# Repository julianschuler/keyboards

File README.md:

# Keyboards

This repository contains the code, cases and co. of the keyboards I have built.

All keyboards in chronological order:

| Name                        | Image                                                 | Description                                                                        |
| --------------------------- | ----------------------------------------------------- | ---------------------------------------------------------------------------------- |
| [Manuform](manuform/)       |           | 50% hand-wired keyboard focussed on ergonomic typing with ortholinear columns      |
| [Ergomin](ergomin/)         |              | 40% PCB based split keyboard focussed on ergonomic typing with ortholinear columns |
| [Concavum](concavum/)       |           | Fully parametric ergonomic split keyboard with automatically generated matrix PCB  |
| [Concavum v2](concavum-v2/) |  | Second revision of the Concavum keyboard with an easy to use customizer            |

## License

This project is licensed under the MIT license, see [`LICENSE.txt`](LICENSE.txt) for further information.

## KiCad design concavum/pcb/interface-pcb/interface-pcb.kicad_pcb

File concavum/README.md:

# Concavum

## Overview
The Concavum is a fully parametric split keyboard featuring an ergonomic layout with ortholinear (non-staggered) columns and concave key wells.

It can be adjusted to have 1-5 rows, 2-6 columns and 1-6 thumb keys per half and provides a script to automatically generate a PCB for the key matrix, so no hand-wiring is required.

Each half has thus 2 PCBs: The automatically generated matrix PCB, which is dependent on key count, offsets, etc., and a generic interface PCB which can be used for all sizes. Both PCBs are connected internally using a FPC cable, the halves are connected externally through a TRRS cable.

## Building the keyboard
### Parts list (excluding the PCBs and complementary components)
The amount of switches and keycaps depends on the number of rows, columns and thumb keys.
* 6-72x keyboard switches (Cherry MX, Gateron, etc.)
* 2-60x DSA keycaps 1U
* 2-12x DSA keycaps 1.5U
* 8x countersunk screws M3x8
* 8x nuts M3
* 8x rubber feet
* 1x TRRS to TRRS cable 30cm (make sure it is the 4-pole variant)
* ~150-350g of PETG filament for the 3D printed case (heavily dependent on the size)

### Adjusting the keyboard
The first step in building a Concavum is to adjust the keyboard to your hand.
Start by installing [OpenSCAD](https://openscad.org/downloads.html) if not already done.
Open the file `case/concavum-case.scad` in OpenSCAD and switch to the Customizer (`Window > Customizer`). Select the preset with the name `keyboard-paramters` in the first drop down menu (the preview should now show a cluster with 6 columns and 3 rows).

Now you can start adjusting the keyboard to your needs, the default values adjusted to my hands should provide a good starting point. Always save your changes to the preset `keyboard-parameters` as the values of this preset will be used for the automatic matrix PCB generation later.

### Printing and testing the case
When you are done with your modifications, render the Case using `F6` and export it as STL or AMF.
Support material is required for printing. However, use support blockers for the nut holders as it is nearly impossible to remove support material from their inside. You can find example print files under [`case/example-print-files`](case/example-print-files) which should give an idea on how to adjust the support material and print settings.

It is highly recommended to print only one half for now, adding the switches and keycaps and testing the feel first. It may take a few iterations, really take your time to find a configuration that fits your hands!

If you are happy with your configuration, you can now print the second half and add the remaining switches and keycaps.

The bottom plate of the keyboard can either be 3D printed as well or e.g. cut out of aluminum. It can thus be either exported as a 3D object or outline using
```
python3 case/export-bottom-plate.py [output file name]
```
where the file extension determines its type (e.g. `bottom-plate.amf` or `bottom-plate.dxf`). In case of cutting, chamfer the holes afterwards using a countersink drill bit to allow the screw heads to sit flush later.

### Generating the PCB
To generate the matrix PCB, install [KiCad 7.0](https://www.kicad.org/download/) and [Python 3](https://www.python.org/downloads/). Afterwards, switch to the `pcb` subfolder and install the Python dependencies by executing
```
python3 -m pip3 install -r requirements.txt
```
You can now generate the matrix PCB using
```
python3 generate-matrix-pcb.py
```
and afterwards export the gerber files for both the matrix and interface PCBs using

```
python3 export-compressed-gerber.py
```

When exporting the gerber files, a DRC is performed. If there is no output, everything worked as expected. If you still would like to inspect the generated matrix PCB, you can open the PCB file using PcbNew (the PCB editor of KiCad):
```
pcbnew matrix-pcb/matrix-pcb-panel.kicad_pcb
```

#### Ordering the PCBs and complementary components
After exporting, you will find two zip files in the `gerber` subfolder: One for the interface PCB and one for the generated matrix PCB.

The two PCB types require different thicknesses: 0.6mm for the matrix PCB and 1.6mm for the interface PCB.
You need at least 2 boards of each type (one type of board for each half).

> **Note:** For the matrix PCB, your PCB manufacturer has to support track widths and minimum clearances of 0.15mm each. In the special case of keyboards with the maximum number of rows, tracks and minimum clearances of 0.13mm each have to be supported.

### Assembly
First, insert the M3 nuts into their holders (you may need to remove a few keys if you have already assembled those during testing).
Afterwards, add the key switches while ensuring that the orientation of the pins is aligned with the holes of the matrix PCB.

To assemble the PCBs, take two interface and two matrix PCBs and lay them each down with different sides facing up. Now you can solder the complementary SMD components onto all four PCBs.
**Important: Only solder the SMD components to the top of each PCB! Otherwise the keyboard will not work!**

*Assembled PCBs and FPC connectors needed for the whole keyboard, with the rails and tabs still connected for the left matrix PCB. The interface PCBs shown are from the deprecated ATmega32u4 variant.*

Afterwards, you can carefully break off the rails and tabs of the matrix PCBs, ideally over an edge. You can now fit the matrix PCBs into the cases, the sides with the diodes and FPC connector facing outwards.
The matrix PCB has to be bend during this procedure. Therefore, start to solder the switches at the top row and work your way down to the bottom rows and the thumb cluster.

Finally, you can add the FPC cables to connect the interface and matrix PCBs of each half and slide the interface PCBs into their dedicated holders.

*Fully assembled keyboard without bottom plates, on the left a half with the (now deprecated) ATmega32u4 variant is shown, on the right the KB2040 variant can be seen.*

The keyboard can now be closed up by screwing on the bottom plate and attaching the rubber feet.

## Building the firmware
### Setting up QMK
The firmware is powered by QMK, [install QMK](https://docs.qmk.fm/#/newbs_getting_started) if not already done.
After the installation, it is necessary to add a symlink to the `qmk` subfolder of this repository to the QMK `keyboards` directory, for linux e.g by
```
ln -s /path/to/concavum/qmk /path/to/qmk/keyboards/concavum
```

Now you should be able to compile the keyboard firmware by executing
```
qmk compile -kb concavum -km default
```

Make sure to have a look at the excellent [QMK documentation](https://docs.qmk.fm/#/newbs_building_firmware) on how to create your own keymap.

### Adjusting the keymap
After creating your first keymap, you can start by setting `MATRIX_ROWS`, `MATRIX_COLS` and `THUMB_KEYS` in `qmk/keymaps/<github_username>/config.h` according to your keyboard matrix.

Next, head over to `qmk/keymaps/<github_username>/keymap.c` and adjust the keymap to your liking. Make sure the amount of keys is correct, especially when you modified the above values compared to the default.

When you are finished, you can connect the keyboard via USB.
Put the KB2040 into the bootloader mode by holding the boot button and tapping the reset button, the KB2040 should now show up as a flash drive. After mounting the drive you can flash the firmware using
```
qmk flash -kb concavum -km <github_username>
```

### Reflashing the firmware
When flashing e.g. a new keymap to the Concavum, it has to be put into the bootloader mode. This can be done by hitting a key with the `QK_BOOT` keycode or double tapping the reset button on the KB2040. By default, this `QK_BOOT` keycode can be activated by holding both outermost thumb keys and hitting the key in the lower left corner.

It is highly recommended to keep this `QK_BOOT` keycode in any keymap you create as the physical reset button can only be accessed with the bottom plate removed.

## License

This project is licensed under the MIT license, see [`LICENSE.txt`](../LICENSE.txt) for further information.

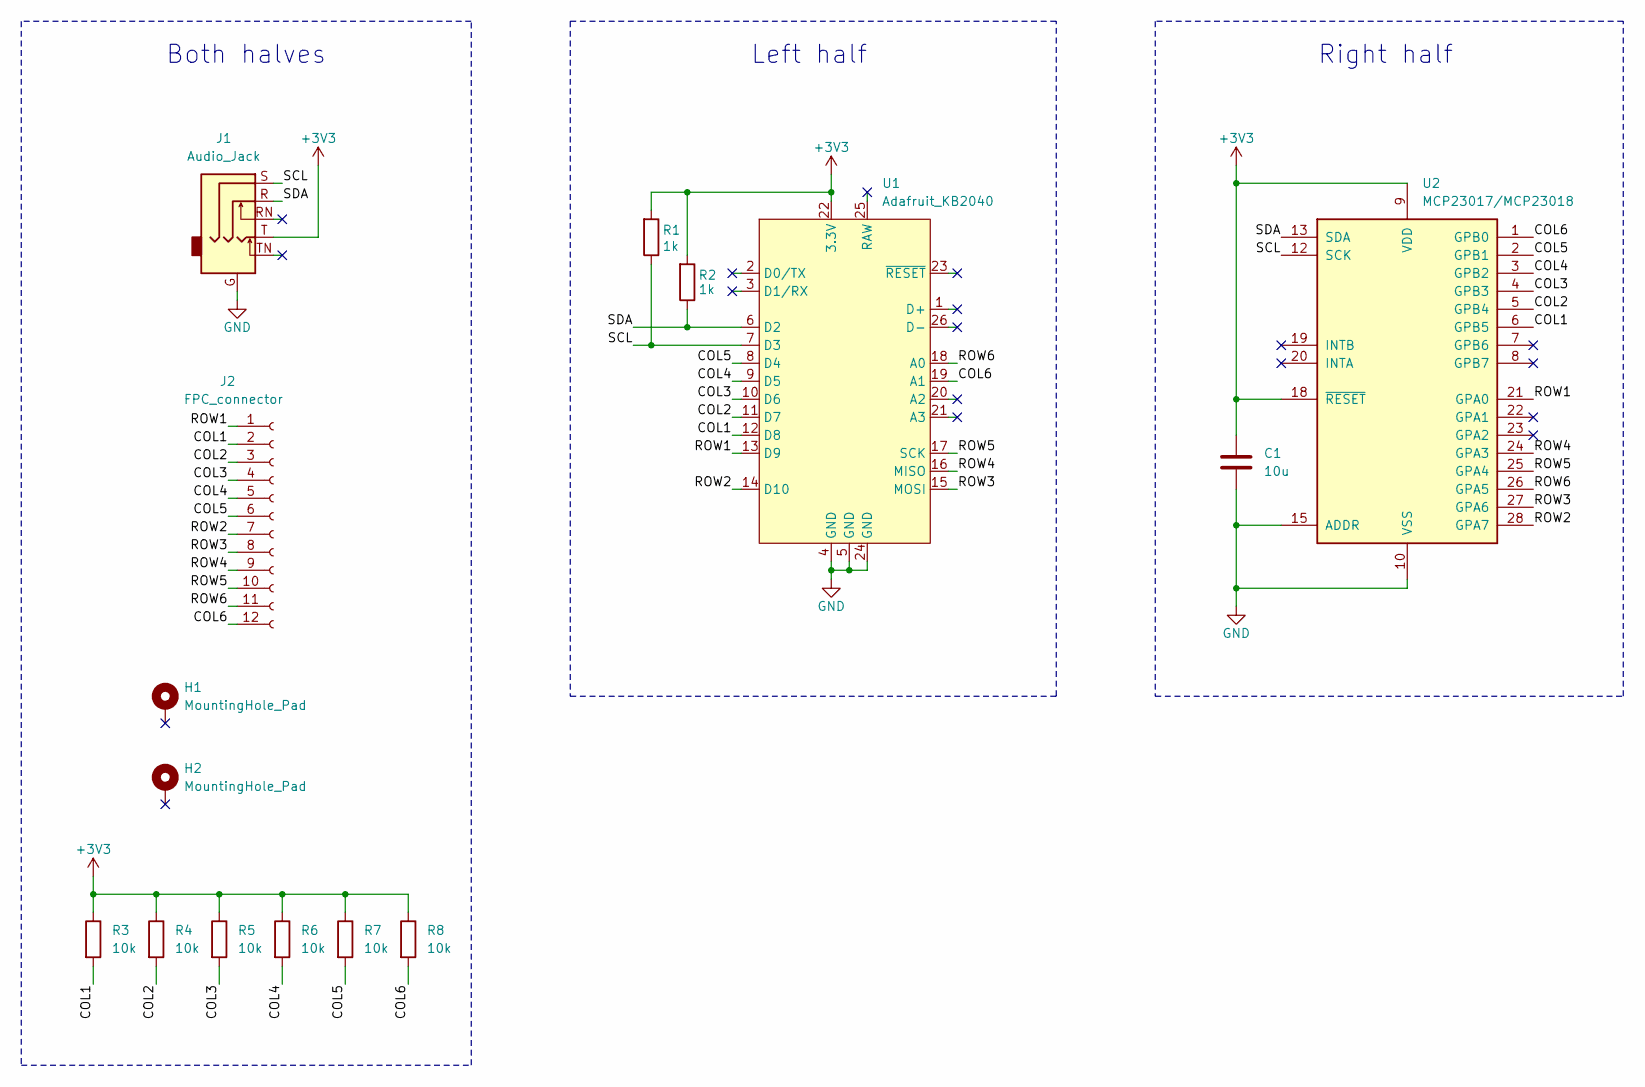
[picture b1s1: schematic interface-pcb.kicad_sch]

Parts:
C1: 10u; C_1206_3216Metric
H1, H2: MountingHole_Pad; MountingHole_2.2mm_M2_Pad_Via
J1: Audio_Jack; Audio_Jack_Dual_Side
J2: FPC_connector; FPC_Connector
R1, R2: 1k; R_1206_3216Metric
R3, R4, R5, R6, R7, R8: 10k; R_1206_3216Metric
U1: Adafruit_KB2040
U2: MCP23017/MCP23018; MCP23017_SO_MCP23018_SO

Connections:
+3V3: C1.1, J1.T, R1.2, R2.2, R3.1, R4.1, R5.1, R6.1, R7.1, R8.1, U1.22 (3.3V), U2.9 (VDD), U2.18 (~RESET)
/COL1: J2.2, R3.2, U1.12 (D8), U2.6 (GPB5)
/COL2: J2.3, R4.2, U1.11 (D7), U2.5 (GPB4)
/COL3: J2.4, R5.2, U1.10 (D6), U2.4 (GPB3)
/COL4: J2.5, R6.2, U1.9 (D5), U2.3 (GPB2)
/COL5: J2.6, R7.2, U1.8 (D4), U2.2 (GPB1)
/COL6: J2.12, R8.2, U1.19 (A1), U2.1 (GPB0)
/ROW1: J2.1, U1.13 (D9), U2.21 (GPA0)
/ROW2: J2.7, U1.14 (D10), U2.28 (GPA7)
/ROW3: J2.8, U1.15 (MOSI), U2.27 (GPA6)
/ROW4: J2.9, U1.16 (MISO), U2.24 (GPA3)
/ROW5: J2.10, U1.17 (SCK), U2.25 (GPA4)
/ROW6: J2.11, U1.18 (A0), U2.26 (GPA5)
/SCL: J1.S, R1.1, U1.7 (D3), U2.12 (SCK)
/SDA: J1.R, R2.1, U1.6 (D2), U2.13 (SDA)
GND: C1.2, J1.G, U1.4 (GND), U1.5 (GND), U1.24 (GND), U2.10 (VSS), U2.15 (ADDR)

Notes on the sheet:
Right half
Left half
Both halves

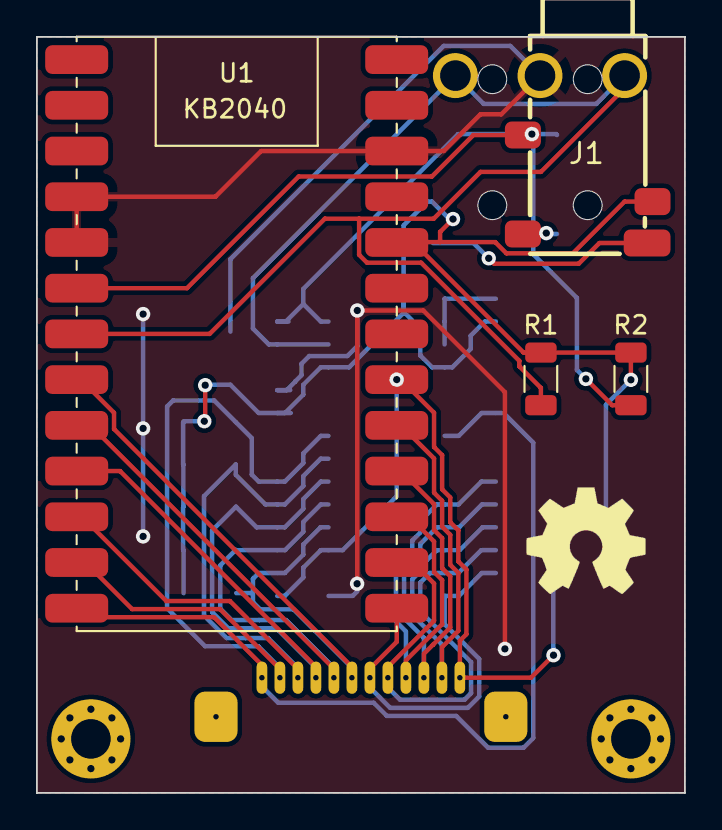
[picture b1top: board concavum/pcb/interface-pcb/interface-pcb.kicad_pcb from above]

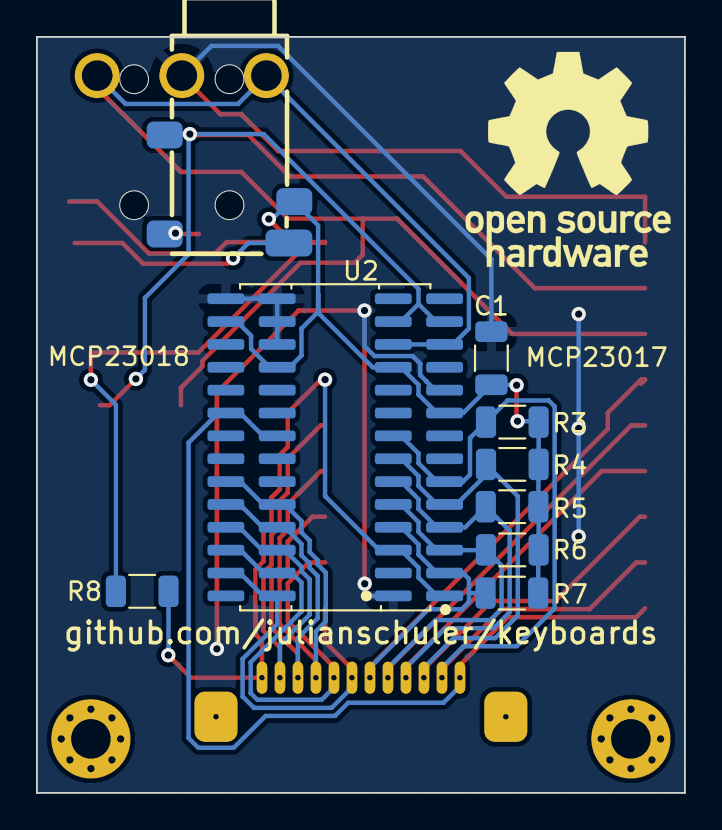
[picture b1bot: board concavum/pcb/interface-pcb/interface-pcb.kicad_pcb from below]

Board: 2 copper layers, 36.0 x 42.0 mm, 15 parts (8 on the bottom side), 16 nets.

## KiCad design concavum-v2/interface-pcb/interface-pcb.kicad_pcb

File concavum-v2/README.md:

# Concavum v2

## Overview

The Concavum v2 is a fully parametric split keyboard featuring an ergonomic layout with ortholinear (non-staggered) columns and concave key wells.

The centerpiece of the Concavum v2 is its customizer: It allows for changing all kinds of parameters like the number of columns, rows and thumb keys, the curvature, the distance between keys and many more.
It generates 3D printing files for the case, a PCB for connecting the key switches and configuration files for the keyboard firmware.

## Building your own

First, use the [Concavum customizer](https://github.com/julianschuler/concavum-customizer) to configure your Concavum to your liking.

When you are finished with configuring the keyboard, use the export button at the top right of the configuration panel to export all model files.
Extract the exported ZIP archive to a folder and switch to it.

### Parts list

You can find a detailed parts list in the file `bom.csv` in the export.

### Case

The case of the Concavum is 3D printed, you can find the corresponding files in the `case` subfolder of the export.
Since both halves are symmetric, only the 3D printing files for the right half are included in the export.
Mirror the files along the X axis in your slicer to print the left half.

The cases of both halves should be printed in the default orientation and using support material.
For my build, I used [Prusament PETG Galaxy Black](https://www.prusa3d.com/product/prusament-petg-prusa-galaxy-black-1kg/).

The bottom plates may either be 3D printed or laser cut.
Currently, the customizer only exports a 3D printing file for the bottom plate.
You can use [OpenSCAD](https://openscad.org/) with the provided `bottom_plate_to_dxf.scad` script to generate a DXF file for laser cutting:

```sh
openscad -o bottom_plate.dxf bottom_plate_to_dxf.scad
```

For my build, I ordered the bottom plates to be laser cut out of 3mm thick aluminum sheet.

### PCBs

The Concavum uses two types of PCBs in each half.
The interface PCB houses the keyboard controller, a TRRS and FFC connector and is the same for all Concavum keyboards.
You can find the KiCAD files of the interface PCB in the [`interface-pcb`](interface-pcb) subfolder of this repository.

The matrix PCB is generated by the customizer and specific to each keyboard.
It connects all keys in a matrix and connects to the interface PCB using an FFC cable.

For manufacturing, some break-away tabs should be added to the matrix PCB.
You can generate these tabs using [KiKit](https://yaqwsx.github.io/KiKit/latest/).
Start by [installing the KiKit backend](https://yaqwsx.github.io/KiKit/latest/installation/intro/) and execute the following command in the `pcb` folder of the exported files:

```sh
kikit panelize -p kikit_parameters.json matrix_pcb.kicad_pcb matrix_pcb_panelized.kicad_pcb
```

> [!TIP]
> You can also use KiKit to generate the gerber files from the KiCad files:
> ```sh
> kikit export gerber matrix_pcb_panelized.kicad_pcb matrix_pcb
> kikit export gerber interface_pcb.kicad_pcb interface_pcb
> ```

The two PCB types require different thicknesses.
When ordering, select 0.6mm for the matrix PCB and 1.6mm for the interface PCB.
You need at least 2 boards of each type, one of each type per half.

### Assembly

First, install the heat set inserts into the provided holes.
Add the key switches to the case, making sure that the orientation of the pins is aligned with the holes in the matrix PCB.

Next, assemble the interface and matrix PCBs.
All PCBs are designed to be assembled from only one side.
Lay down two pairs of interface and matrix PCBs with different sides facing up in each pair.
Solder all components on the top facing sides of each PCB, leaving the respective bottom sides unpopulated.
The assembled PCBs should be symmetric to each other.

Afterwords, carefully break off the tabs of the matrix PCBs.

*Picture of the assembled matrix and interface PCBs for both halves, with the tabs of the left matrix PCB still connected. The FFC cables connecting the matrix and interface PCBs within each half are shown below the right matrix PCB.*

Insert the matrix PCBs into the cases such that the sides with the diodes and FFC connector face outwards.
For each half, solder the matrix PCB to all keys, pushing it against each key while soldering.
Start with the home row and work your way up and down the columns and to the thumb cluster.

Finally, connect the interface and matrix PCBs of each half using the FFC cables and insert the interface PCBs into their dedicated holders.

*Picture of the fully assembled keyboard without bottom plates. Depending on the thumb cluster position, introducing a loop into the FFC cables as shown in the picture may be necessary to avoid kinks in the cables.*

Use a chamfer bit to create countersinks in the bottom plate holes to make the screws sit flush with them.
Screw on the bottom plate and attach the rubber feet to finish the build.

## Firmware

### Setting up QMK

The firmware is powered by QMK, [install QMK](https://docs.qmk.fm/#/newbs_getting_started) if not already done.

After the installation, rename the `qmk` folder of the export to `concavum` and move it to the `keyboards` folder in the QMK home.

You should now be able to compile the keyboard firmware using the following:

```sh
qmk compile -kb concavum -km default
```

Make sure to have a look at the excellent [QMK documentation](https://docs.qmk.fm/#/newbs_building_firmware) on how to create your own keymap.

### Flashing

To flash the firmware to the Concavum, connect the left half via USB and put the KB2040 into DFU mode by holding the boot button and tapping the reset button.
The KB2040 should now show up as a flash drive.

Mount the drive and flash the default firmware using the following:

```sh
qmk flash -kb concavum
```

Repeat the same process for the right half.

### Reflashing

To for example update the keymap, the firmware has to be reflashed.
When QMK is running on the Concavum, there are multiple ways to put the keyboard into DFU mode for reflashing:

- Press a key with the `QK_BOOT` keycode (not present in the default keymap)
- For the left half: Hold down the top left key when plugging the left half in
- For the right half: Hold down the top right key when plugging the right half in
- Double tap the reset button on the KB2040 (requires removing the bottom plate)

## License

This project is licensed under the MIT license, see [`LICENSE.txt`](../LICENSE.txt) for further information.

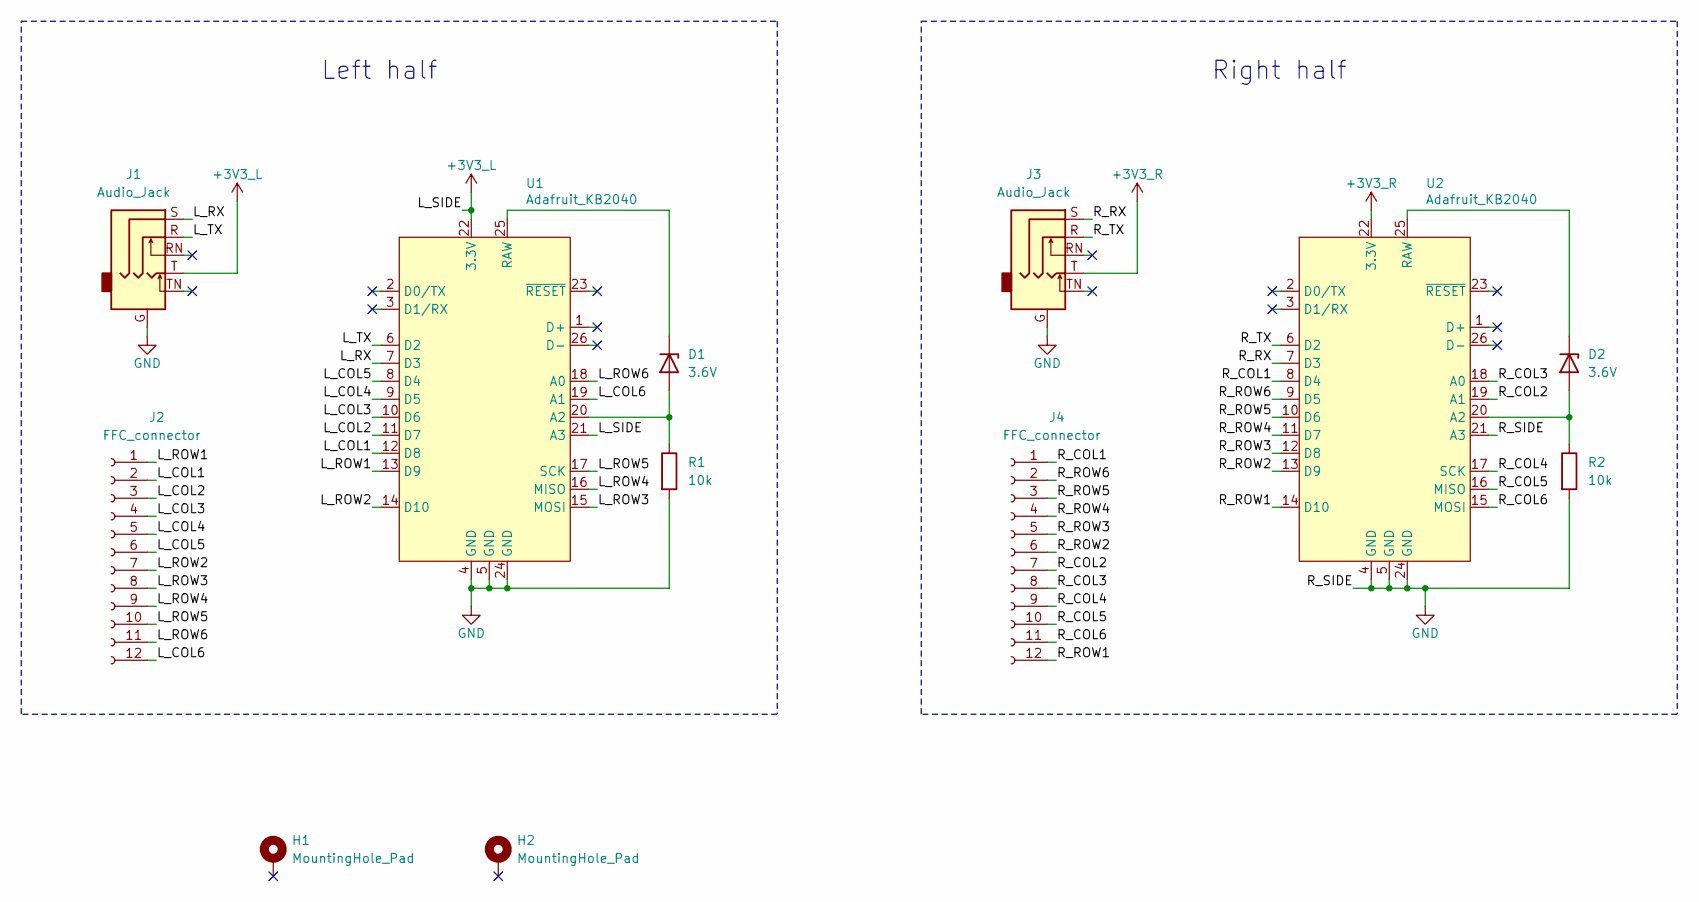
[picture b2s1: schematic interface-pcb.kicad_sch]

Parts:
D1, D2: 3.6V; D_MiniMELF
H1, H2: MountingHole_Pad; MountingHole_2.2mm_M2_Pad_Via
J1, J3: Audio_Jack
J2, J4: FFC_connector; FPC_Connector
R1, R2: 10k; R_1206_3216Metric
U1, U2: Adafruit_KB2040

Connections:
+3V3_L: J1.T, U1.21 (A3), U1.22 (3.3V)
+3V3_R: J3.T, U2.22 (3.3V)
/L_COL1: J2.2, U1.12 (D8)
/L_COL2: J2.3, U1.11 (D7)
/L_COL3: J2.4, U1.10 (D6)
/L_COL4: J2.5, U1.9 (D5)
/L_COL5: J2.6, U1.8 (D4)
/L_COL6: J2.12, U1.19 (A1)
/L_ROW1: J2.1, U1.13 (D9)
/L_ROW2: J2.7, U1.14 (D10)
/L_ROW3: J2.8, U1.15 (MOSI)
/L_ROW4: J2.9, U1.16 (MISO)
/L_ROW5: J2.10, U1.17 (SCK)
/L_ROW6: J2.11, U1.18 (A0)
/L_RX: J1.S, U1.7 (D3)
/L_TX: J1.R, U1.6 (D2)
/R_COL1: J4.1, U2.8 (D4)
/R_COL2: J4.7, U2.19 (A1)
/R_COL3: J4.8, U2.18 (A0)
/R_COL4: J4.9, U2.17 (SCK)
/R_COL5: J4.10, U2.16 (MISO)
/R_COL6: J4.11, U2.15 (MOSI)
/R_ROW1: J4.12, U2.14 (D10)
/R_ROW2: J4.6, U2.13 (D9)
/R_ROW3: J4.5, U2.12 (D8)
/R_ROW4: J4.4, U2.11 (D7)
/R_ROW5: J4.3, U2.10 (D6)
/R_ROW6: J4.2, U2.9 (D5)
/R_RX: J3.S, U2.7 (D3)
/R_TX: J3.R, U2.6 (D2)
GND: J1.G, J3.G, R1.2, R2.2, U1.4 (GND), U1.5 (GND), U1.24 (GND), U2.4 (GND), U2.5 (GND), U2.21 (A3), U2.24 (GND)
unnamed: D1.2 (A), R1.1, U1.20 (A2)
unnamed: D1.1 (K), U1.25 (RAW)
unnamed: D2.2 (A), R2.1, U2.20 (A2)
unnamed: D2.1 (K), U2.25 (RAW)

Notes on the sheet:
Left half
Right half

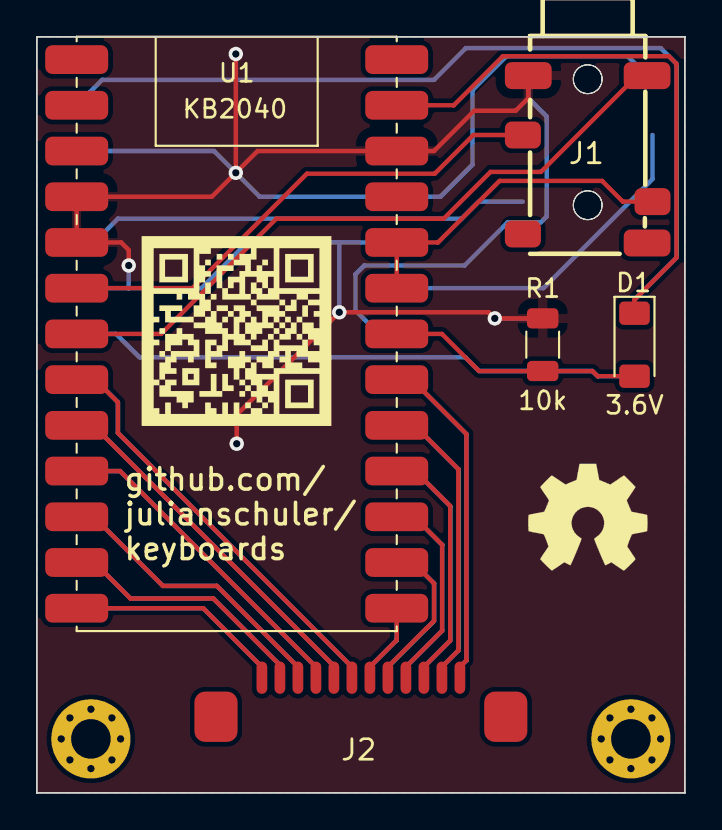
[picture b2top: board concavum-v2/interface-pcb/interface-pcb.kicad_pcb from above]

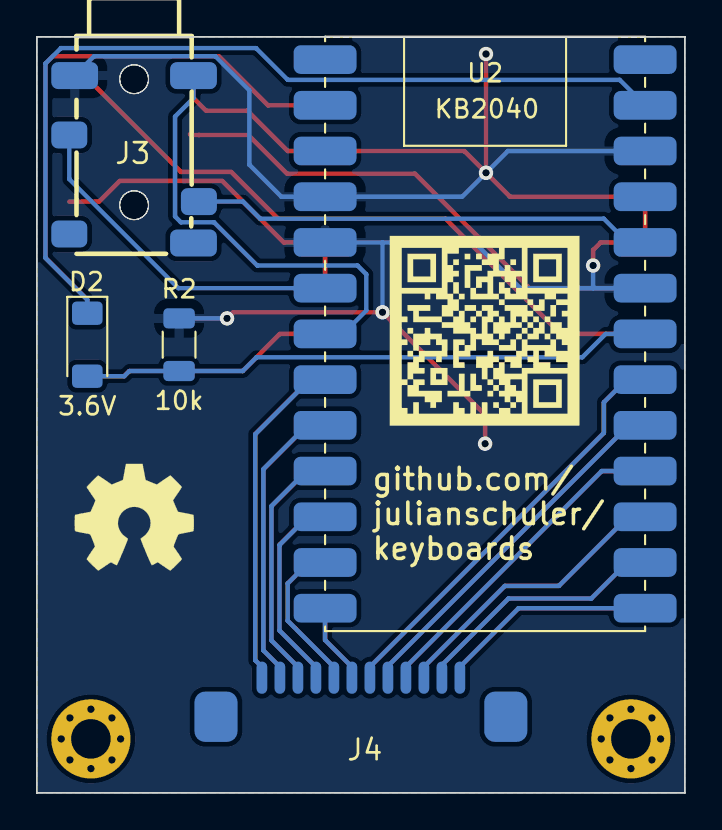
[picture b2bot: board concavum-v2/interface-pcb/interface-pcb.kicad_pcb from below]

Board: 2 copper layers, 36.0 x 42.0 mm, 12 parts (5 on the bottom side), 35 nets.

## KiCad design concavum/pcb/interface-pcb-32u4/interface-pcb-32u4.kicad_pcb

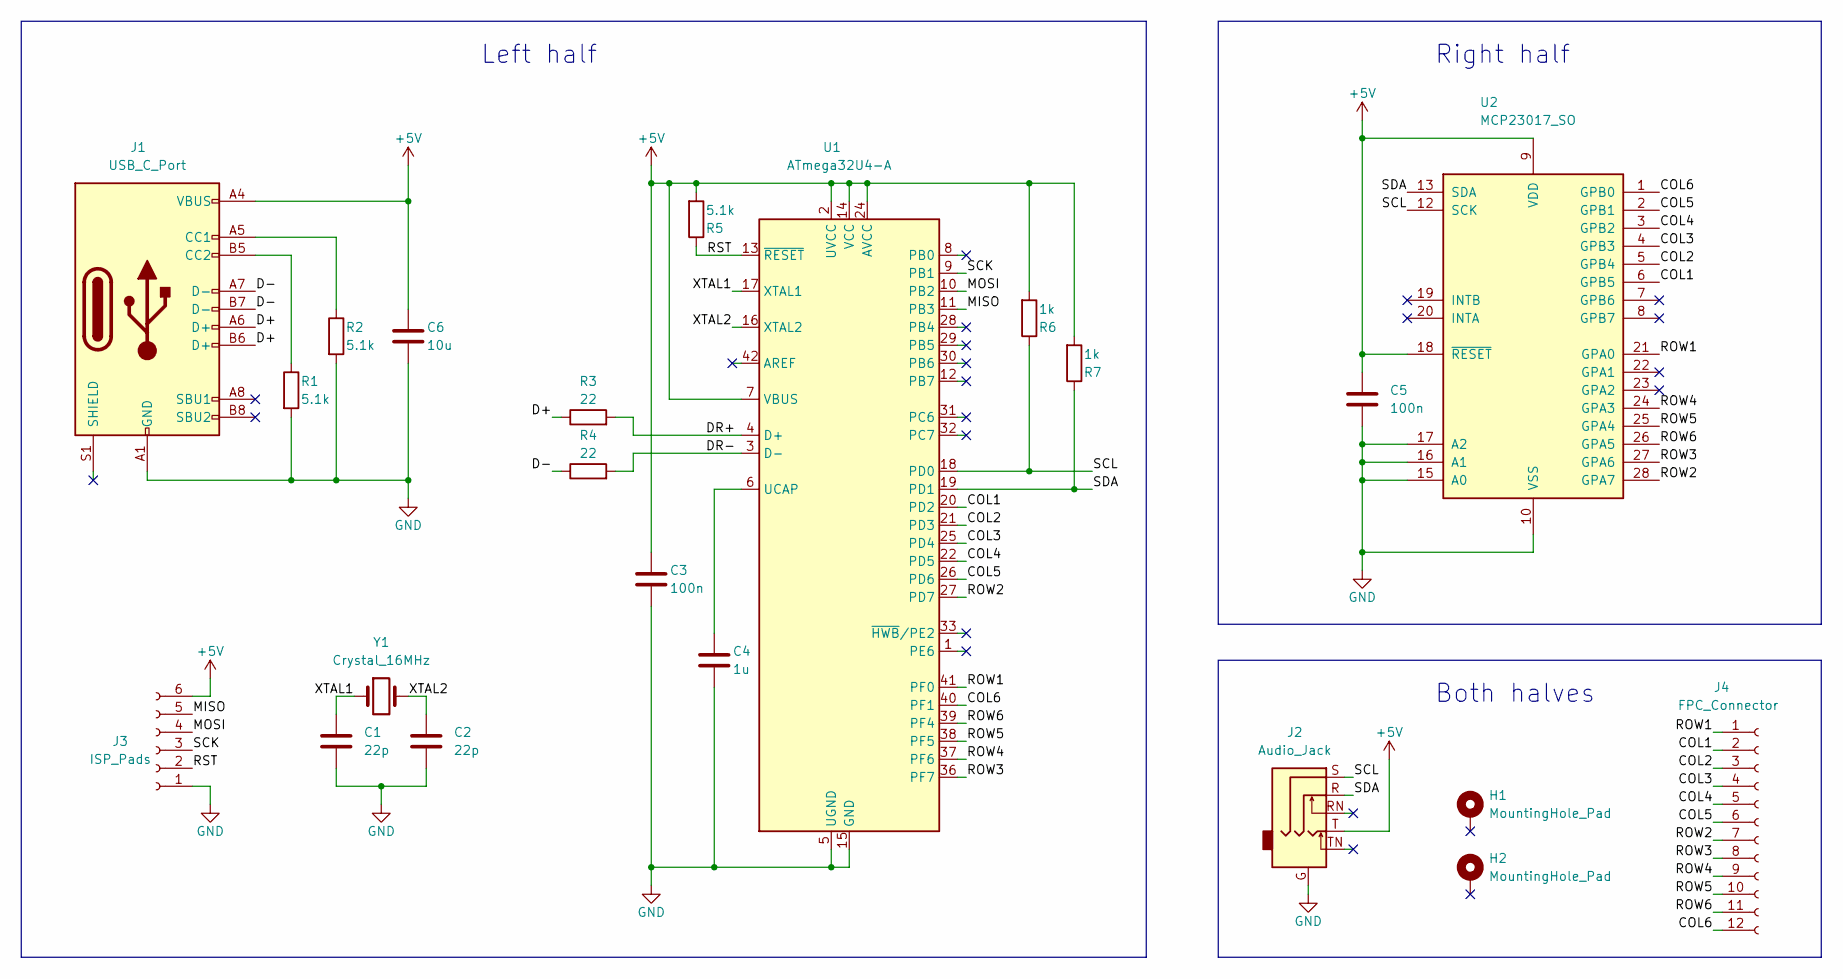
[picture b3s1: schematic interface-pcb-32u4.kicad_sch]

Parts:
C1, C2: 22p; C_0603_1608Metric
C3, C5: 100n; C_0603_1608Metric
C4: 1u; C_0603_1608Metric
C6: 10u; C_0603_1608Metric
H1, H2: MountingHole_Pad; MountingHole_2.2mm_M2_Pad_Via
J1: USB_C_Port; USB_C_Receptacle_HRO_TYPE-C-31-M-12
J2: Audio_Jack; Audio_Jack_Dual_Side
J3: ISP_Pads
J4: FPC_Connector
R1, R2, R5: 5.1k; R_0603_1608Metric
R3, R4: 22; R_0603_1608Metric
R6, R7: 1k; R_0603_1608Metric
U1: ATmega32U4-A; TQFP_44_Rounded_Pads
U2: MCP23017_SO; SOIC-28W_7.5x17.9mm_P1.27mm
Y1: Crystal_16MHz; Crystal_HC49-4H_Vertical

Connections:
+5V: C3.1, C5.1, C6.1, J1.A4 (VBUS), J1.A9 (VBUS), J1.B4 (VBUS), J1.B9 (VBUS), J2.T, J3.6, R5.2, R6.2, R7.2, U1.2 (UVCC), U1.7 (VBUS), U1.14 (VCC), U1.24 (AVCC), U1.34 (VCC), U1.44 (AVCC), U2.9 (VDD), U2.18 (~RESET)
/COL1: J4.2, U1.20 (PD2), U2.6 (GPB5)
/COL2: J4.3, U1.21 (PD3), U2.5 (GPB4)
/COL3: J4.4, U1.25 (PD4), U2.4 (GPB3)
/COL4: J4.5, U1.22 (PD5), U2.3 (GPB2)
/COL5: J4.6, U1.26 (PD6), U2.2 (GPB1)
/COL6: J4.12, U1.40 (PF1), U2.1 (GPB0)
/D+: J1.A6 (D+), J1.B6 (D+), R3.1
/D-: J1.A7 (D-), J1.B7 (D-), R4.1
/DR+: R3.2, U1.4 (D+)
/DR-: R4.2, U1.3 (D-)
/MISO: J3.5, U1.11 (PB3)
/MOSI: J3.4, U1.10 (PB2)
/ROW1: J4.1, U1.41 (PF0), U2.21 (GPA0)
/ROW2: J4.7, U1.27 (PD7), U2.28 (GPA7)
/ROW3: J4.8, U1.36 (PF7), U2.27 (GPA6)
/ROW4: J4.9, U1.37 (PF6), U2.24 (GPA3)
/ROW5: J4.10, U1.38 (PF5), U2.25 (GPA4)
/ROW6: J4.11, U1.39 (PF4), U2.26 (GPA5)
/RST: J3.2, R5.1, U1.13 (~RESET)
/SCK: J3.3, U1.9 (PB1)
/SCL: J2.S, R6.1, U1.18 (PD0), U2.12 (SCK)
/SDA: J2.R, R7.1, U1.19 (PD1), U2.13 (SDA)
/XTAL1: C1.1, U1.17 (XTAL1), Y1.1
/XTAL2: C2.1, U1.16 (XTAL2), Y1.2
GND: C1.2, C2.2, C3.2, C4.2, C5.2, C6.2, J1.A1 (GND), J1.A12 (GND), J1.B1 (GND), J1.B12 (GND), J2.G, J3.1, R1.2, R2.2, U1.5 (UGND), U1.15 (GND), U1.23 (GND), U1.35 (GND), U1.43 (GND), U2.10 (VSS), U2.15 (A0), U2.16 (A1), U2.17 (A2)
unnamed: C4.1, U1.6 (UCAP)
unnamed: J1.A5 (CC1), R2.1
unnamed: J1.B5 (CC2), R1.1

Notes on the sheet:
Right half
Left half
Both halves

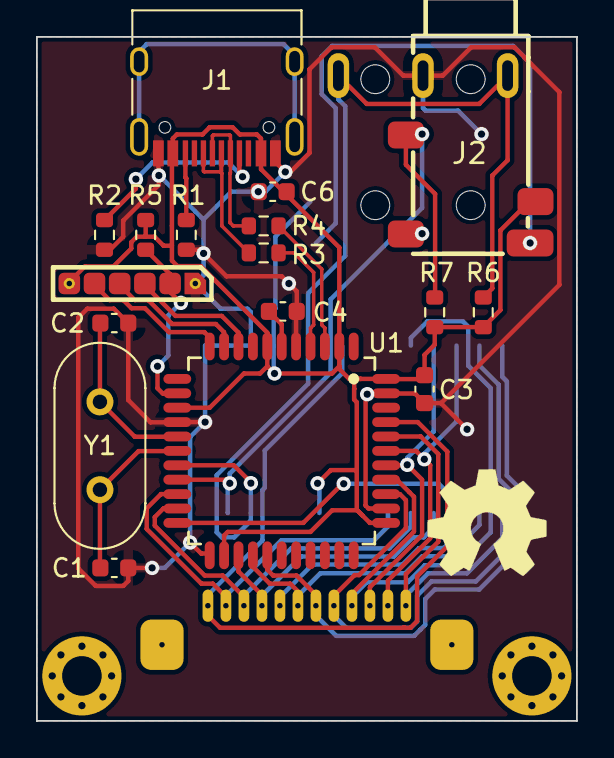
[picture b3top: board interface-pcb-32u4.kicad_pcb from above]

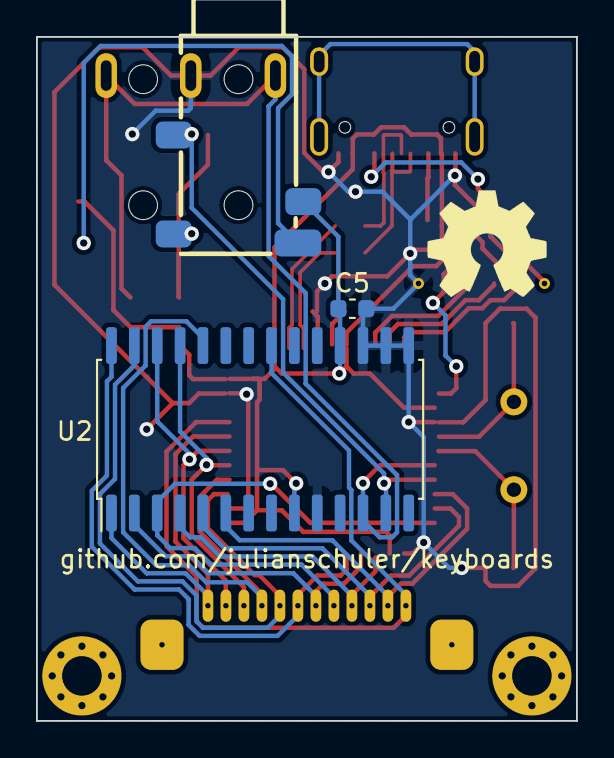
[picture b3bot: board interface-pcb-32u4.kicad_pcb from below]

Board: 2 copper layers, 30.0 x 38.0 mm, 22 parts (2 on the bottom side), 29 nets.

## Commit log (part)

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2021-06-11 Add manuform files
2021-06-11 Add ergomin files
2021-06-11 Add LICENSE.txt
2021-06-11 Add README.md
2021-06-14 Add README.md for manuform
2021-06-14 Split keymaps into personal and default
2021-06-14 Add README.md for ergomin
2021-06-14 Correct mistakes in README
2021-06-15 Add build instructions for the ergomin
2021-06-15 Add 3MF case files
2021-06-15 Add references to keyboards in main README
2021-06-15 Add case files for manuform
2021-06-29 Add images
2021-06-30 Update ergomin schematic
2021-06-30 Add/modify WASD (gaming) layers
2021-07-09 Modify case to match current PCB layout
2021-07-11 Adjust ergomin description from 50% to 40% keyboard
2021-07-26 Modify WASD and movement layer
2021-08-23 Set up one shot timing and tapping terms
2021-09-05 Add shortcut for journal
2021-09-05 Seperate rules.mk and add chording for symbols
2021-09-15 Add concavum case file
2021-10-29 Add first pcb generation scripts
2021-10-30 Finish vertical pcb column connectors
2021-11-01 Swap number and square bracket combos
2021-11-01 Swap _ and ß and adjust shortcuts
2021-11-22 Replace program shortcuts with general purpose ones
2021-11-22 Fix shift being sent when sending ctrl+backspace
2021-12-06 Add interactive test for bending approximation
2021-12-06 Fix arcs and adjust rendering parameters
2021-12-22 Add visualization for the bending thumb connector
2021-12-22 Improve thumb connector arc radius calculation
2021-12-22 Finish pcb thumb connector
2021-12-23 Structure code and improve bending visualisation
2021-12-23 Add thumb connector anker offset values
2021-12-24 Add flake8 config file
2021-12-24 Add key matrix pcb generation script
2021-12-24 Improve code structure and documentation
2021-12-28 Add .gitignore
2021-12-28 Add command line file generation and gerber export
2021-12-28 Remove old version of renamed generate_pcb.py
2021-12-28 Use dual sided and centered key switch footprint
2021-12-29 Add pcb key positioning for the thumb cluster
2022-01-10 Move compressed gerber exporter to separate file
2022-01-10 Add automatic net creation
2022-01-11 Add first automatically placed traces
2022-01-12 Improve column connections
2022-01-12 Output column connector values
2022-01-13 Add thumb row tracks
2022-01-14 Refactor column connector generation
2022-01-14 Add column connector tracks
2022-01-15 Modify connector structure
2022-01-15 Simplify switch footprint
2022-01-15 Remove plugin functionalities from pcb generator
    Previously the script could still be executed as a pcbnew scripting
    plugin, this deprecated functionality has been finally removed in this commit.
2022-01-15 Add interface PCB files
2022-01-16 Add FPC connector footprint and placement
2022-01-16 Add row connecting tracks
2022-01-17 Make row connectors independant of pad size
2022-01-18 Separate path generation functions from main class
2022-01-18 Refactor row track paths by using offset_path()
2022-01-19 Add chamfers to the outermost row connector tracks
2022-01-19 Improve edge case row connector handling
2022-01-20 Add tracks between columns and their connectors
2022-01-20 Add tracks between columns
2022-01-24 Add chamfers to the column connecting tracks
2022-01-25 Add tracks between FPC connector and left columns
2022-01-25 Ensure row and column counts don't exceed maxima
2022-01-25 Add FPC connector pad to key matrix PCB
2022-01-26 Add tracks going through the thumb connector
2022-01-26 Add tracks between FPC and thumb connector
2022-01-26 Add tracks between the thumb cluster and connector
2022-01-27 Improve footprints by rounding pad corners and co.
2022-01-28 Add in-depth parameter descriptions and a check
2022-01-28 Remove old unnecessary nets
2022-01-28 Split up function adding column tracks to FPC pads
2022-01-28 Improve the track between center column and FPC
2022-01-28 Move tracks slighly to comply with DRC
2022-01-28 Add assertions to ensure the described constraints
2022-01-29 Round DXF line points for panelization
2022-01-30 Use kikit to add rails and tabs for manufacturing
2022-01-30 Adjust distances to account for manufacturing
2022-01-30 Fix generation for less than 6 columns
2022-01-30 Unify unit handling, unit is now always denoted
2022-01-30 Move template file and add DRC settings
2022-01-30 Add extra cuts along the frame
2022-01-30 Add text to the frame
2022-01-31 Specify tab placement for the thumb cluster
2022-01-31 Add python package dependencies
2022-01-31 Improve column connectors to account for routing
2022-01-31 Move and extend parameter checks
2022-01-31 Redo interface PCB using KiCad
2022-01-31 Add a 10µF capacitor as desrcibed in the datasheet
2022-02-01 Improve footprints
2022-02-01 Ignore overlap during DRC
2022-02-01 Select all layers visible as default
2022-02-01 Simplify gerber export script by using KiKit
2022-02-02 Change port expander row and column pins
2022-02-03 Add QMK configuration files and scripts
2022-02-03 Adjust finger cluster column nets to thumb cluster
2022-02-03 Exclude all tabs to the right of the FPC connector
2022-02-03 Add own and default keymap
2022-02-03 Move Alt key and adjust default keymap to own
2022-02-03 Move Alt key and replace BSP_ALT with SS_ALT
2022-02-03 Remove info.json files as the QMK API isn't used
2022-02-03 Adjust manuform layout to ergomin layout
2022-02-05 Allow setting a tenting angle for the X and Y axis
2022-02-05 Adjust thumb cluster nut holder placement
2022-02-06 Add FPC connector visualization
2022-02-06 Restructure code to use with OpenSCAD customizer
2022-02-07 Flag to build key matrix PCB and variable cleanup
2022-02-07 Correct include guard name
2022-02-07 Add License
2022-02-07 Rename bending approximation script
2022-02-08 Add M2 mounting holes
2022-02-09 Add OSHW logo and URL
2022-02-09 Improve colors
2022-02-15 Use customizer preset when exporting bottom plate
2022-02-15 Adjust keycode names to newest QMK version
2022-02-15 Move keymap specific settings to separate files
2022-02-15 Remove deprecated fix for MO()
2022-02-15 Enable combos for the manuform
2022-02-15 Correct number of columns used to save the keymaps
2022-02-15 Remove unnecessary backslashes
2022-02-18 Beautify Concavum keyboard layout
2022-02-18 Adjust upper layers to other keyboards
2022-02-18 Disable now unused unicode input
2022-02-18 Beautify Ergomin and Manuform keyboard layouts
2022-02-18 Correct minor mistake in layout description
2022-02-18 Correct errors in keymaps and combos
2022-02-18 Rework symbol layer accommodating symbol frequency
2022-02-21 Adjust colors
2022-02-21 Correct port offset and increase clearance
2022-02-21 Improve bottom plate by adding bolt head cutouts
2022-03-10 Adjust shell thickness for stability/print quality
2022-03-10 Rename interface pcb to indicate 32u4 variant
2022-03-10 Rename footprints to match KiCad naming scheme
2022-03-10 Add KiCad symbol and footprint for Adafruit KB2040
2022-03-10 Modify KB2040 symbol
2022-03-10 Add KB2040 based interface PCB
2022-03-10 Add interface PCB type selection for gerber export
2022-03-10 Replace elongated holes with ordinary ones
2022-03-12 Fix invalid matrix error
2022-03-12 Increase matrix scan rate and improve matrix code
2022-03-13 Rewrite port expander code to only use the I2C API
2022-03-14 Add value for manufacturer field in USB settings
2022-03-14 Add support for the KB2040 variant in QMK
2022-03-14 Add files describing MCU and HAL config changes
2022-03-16 Activate entering the bootloader with a double tap
2022-03-18 Add flag for selecting between interface variants
2022-03-22 Replace RESET keycode with QK_BOOT
2022-03-22 Update README to differentiate between variants
2022-03-22 Improve notes for the ATmega32u4 variant in README
2022-03-26 Fix wrong variable used for bottom plate thickness
2022-03-28 Add reference to Concavum in root README.md
2022-04-03 Add startup delay for port expander
2022-04-03 Add option to use MCP23018 instead of MCP23017
2022-04-03 Correct track clearances
2022-04-21 Change deselecting row behaviour for port expander
    Deselected rows are now set from output to input instead of from low to high.
2022-04-22 Fix incorrect usage of LAYOUT instead of LAYER
2022-04-25 Generate concavum.h via python script
    For each valid combination of MATRIX_ROWS, MATRIX_COLS and THUMB_KEYS
    the macro LAYOUT is defined separately. This removes the need for the LAYER,
    ROW and T_ROW macros. The keymap description now follows the QMK default.
2022-04-25 Add note about MCP23017/MCP23018 support
2022-05-08 Change FPC connector pinout to increase clearances
2022-05-08 Fix incorrect row track placement for lower half
2022-05-10 Increase tab thickness and tab count
2022-06-16 Improve generation of the thumb cluster connector
    The theoretical foundations of the thumb connector have been mostly reworked: The bending approximation is now more accurate, mathematically simpler and more robust for all input parameters.
    Furthermore, the visualisation of the bezier curve section has been redone completely using a single polyhedra instead of multiple cubes. The bending approximation is now displayed correctly for all 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
2022-07-04 Adjust QMK config to latest develop branch
2023-03-05 Sort python imports
2023-03-18 Add left hand number layer for gaming
2023-03-18 Clean up and unify modifiers
2023-03-21 Remove deprecated note regarding QMK branch
2023-03-21 Add setup.cfg
2023-03-23 Migrate Manuform to QMK version 0.20.1
2023-03-23 Migrate Ergomin to QMK version 0.20.1
2023-03-23 Migrate Concavum to QMK version 0.20.1
2023-03-23 Match QMK matrix settings to case parameters
2023-03-23 Update license years
2023-03-23 Improve outline drawing by ignoring small lines
2023-03-23 Format python code using black
2023-03-23 Migrate interface PCB to KiCad 7.0
2023-03-23 Migrate matrix PCB generation script to KiCad 7.0
2023-03-25 Format info.json files
2023-03-26 Replace keymap-level info.json files ignored by qmk
2023-03-26 Enable caps word feature
2023-04-02 Add Ergomin hinge
2023-04-03 Replace rotate_vec with rotation_mat
2023-04-07 Correct thumb connector faces orientation
2023-04-09 Add first parts of finger cluster polyhedron
2023-04-14 Add circumference points
2023-04-14 Add corner points
2023-04-16 Improve ordering of circumference points
2023-04-22 Calculate faces for connecting sections
    Calculate faces between columns and circumference points by
    constructing delaunay triangulations for simple polygons in 3D
2023-04-22 Add corner faces
2023-04-23 Add chamfer vertices and faces
2023-04-29 Add secondary chamfer vertices and faces
2023-05-05 Add function to normalize vectors
2023-05-06 Add function for offsetting a polyhedron
2023-07-16 Replace and remove statements with each
2024-01-04 Remove unused functions
2024-01-04 Show WIP improved and new case side by side
2024-10-17 Update license year
2024-10-17 Update interface PCB files to KiCad 8 format
2025-01-23 Reduce startup delay
2025-02-07 WIP [skip ci]
2025-02-07 Use the PCA9555 port expander for the right half
2025-02-07 Move capacitor closer to IC and add second QR code
2025-08-03 Fix incorrect array size
2025-08-06 Move all Manuform QMK config into keyboard.json
2025-08-06 Move all Ergomin QMK config into keyboard.json
2025-08-06 Move Concavum QMK config into keyboard.json
2025-08-06 Update code for right half for use with the PCA9555
2025-08-06 Fix typo
2025-08-07 Add interface PCB files for Concavum v2
2025-08-10 Adjust formatting for thumb keys
2025-08-10 Use a single LICENSE.txt file and update year
2025-08-10 Add QMK config files generated by the customizer
2025-08-10 Reduce combo term to 15ms
2025-08-13 Document the Concavum v2
2025-08-17 Fix custom matrix scan code not being executed
2025-08-17 Update assembly instructions
2025-08-18 Configure bootmagic for switching to DFU mode
2025-08-18 Use a zener diode for VBUS detection circuit
2025-08-18 Update VBUS detection pin
2025-09-03 Replace 2.5V zener diode with 3.6V one
2025-09-03 Update interface PCB files to latest KiCad version
2025-09-03 Add optional pullup resistors to interface PCB
2025-09-03 Only enable combos while space is pressed
2025-09-03 Deduplicate shared code between keymaps
2025-09-03 Activate symbol combos when space is not pressed
2025-09-05 Add images for Concavum v2
2025-09-05 Fix missing capitalization of Concavum
